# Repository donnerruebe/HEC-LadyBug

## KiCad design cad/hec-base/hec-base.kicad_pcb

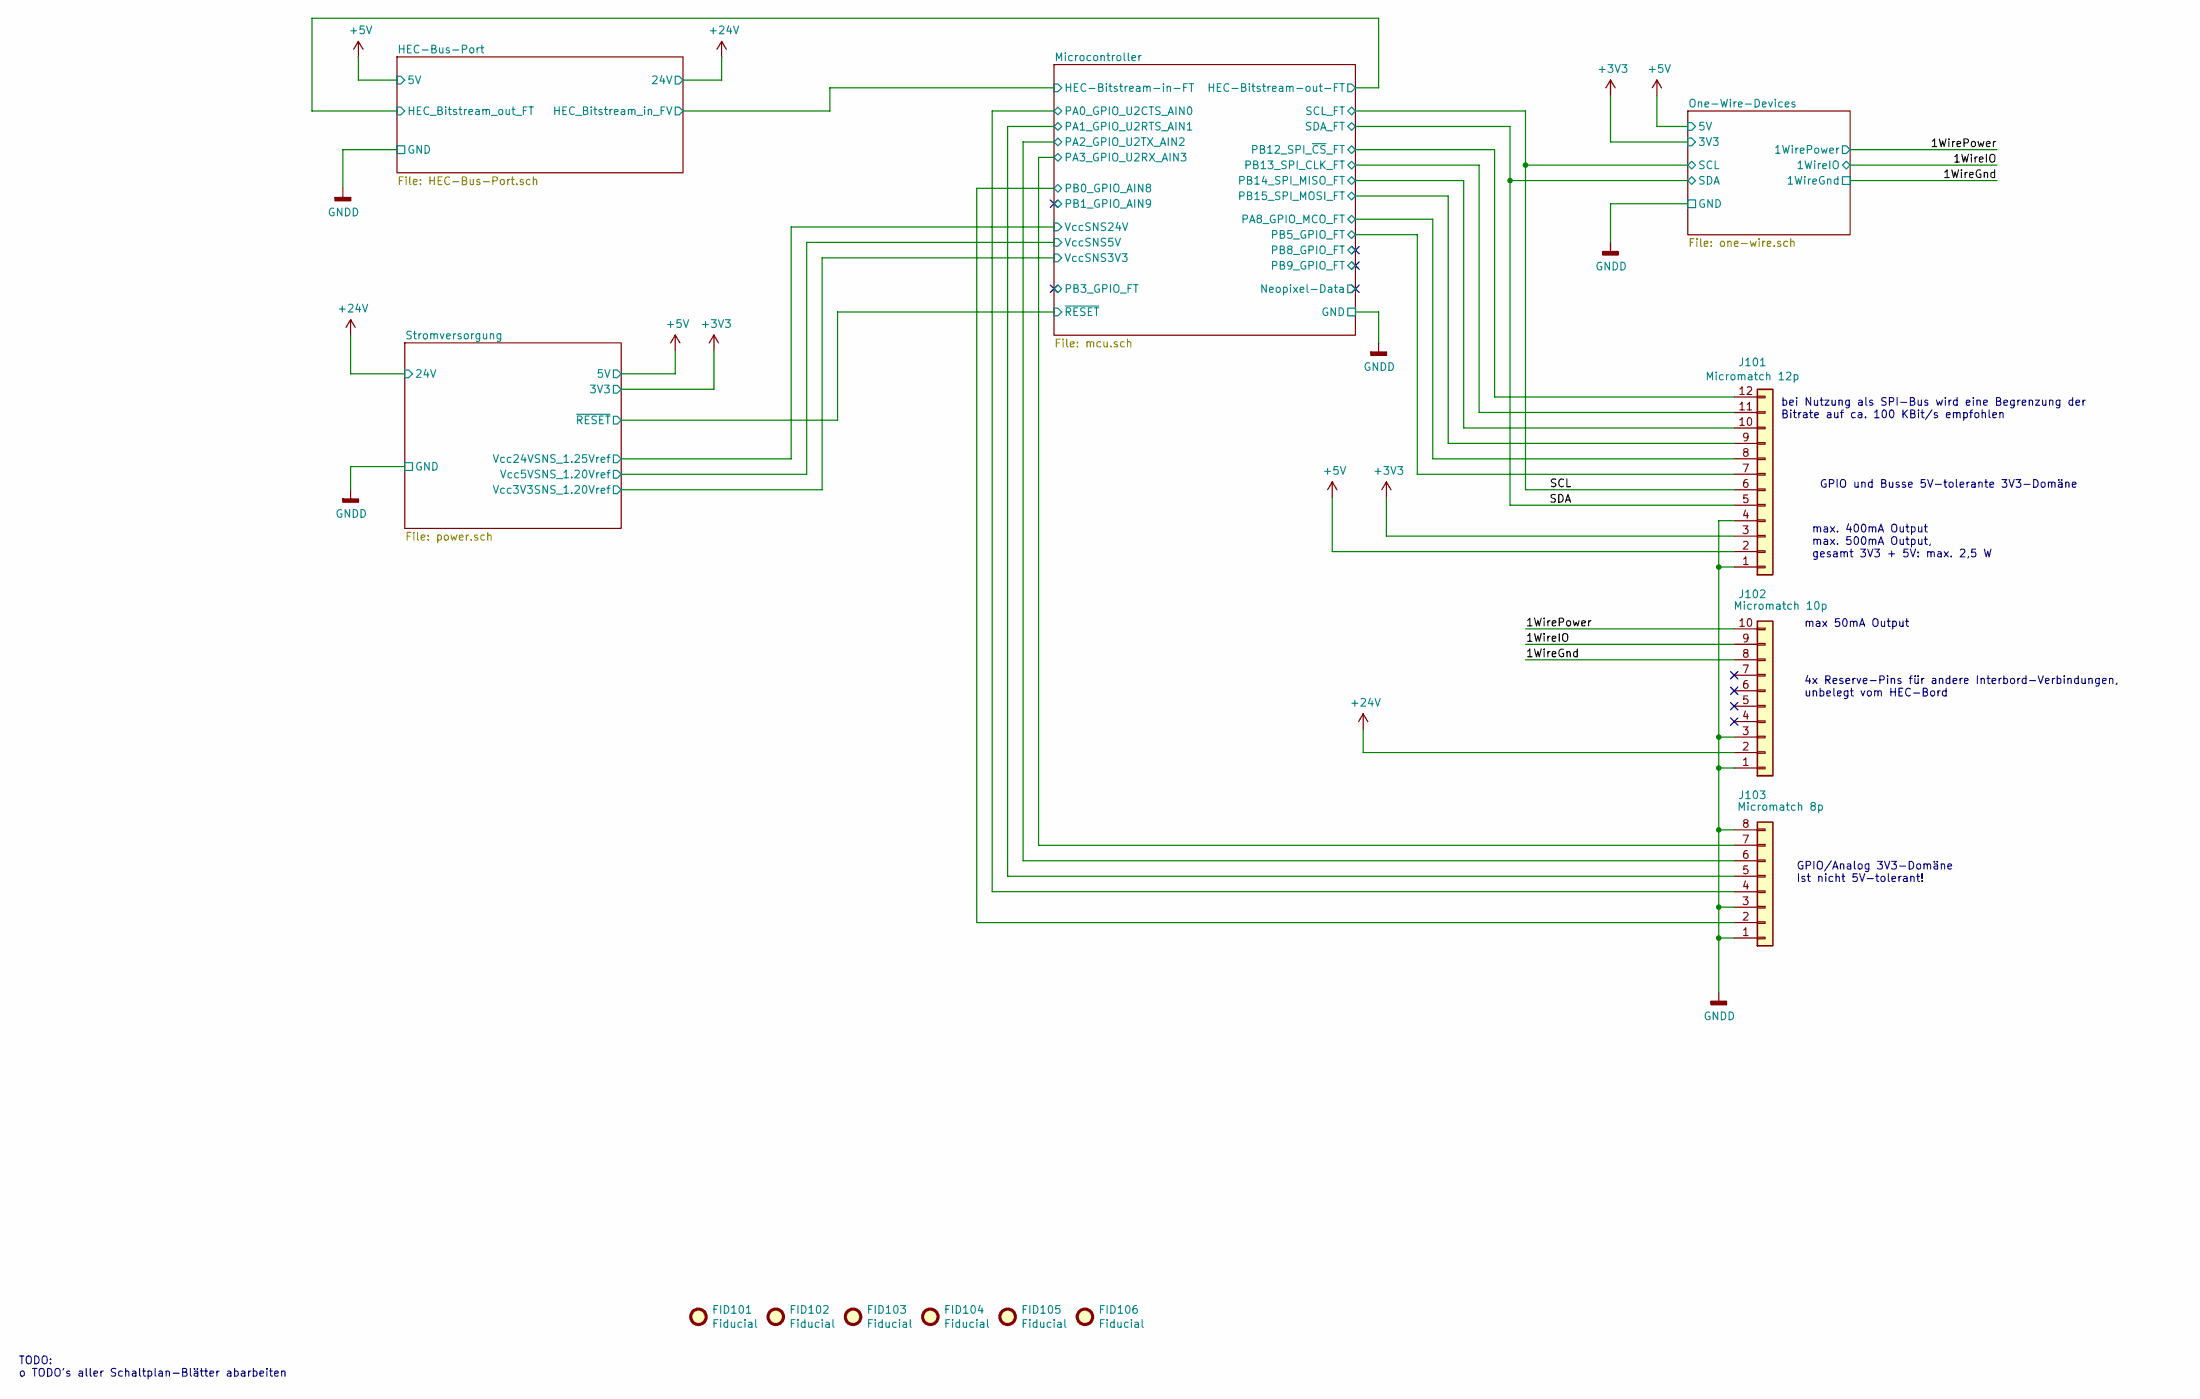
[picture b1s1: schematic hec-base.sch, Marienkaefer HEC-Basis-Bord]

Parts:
FID101, FID102, FID103, FID104, FID105, FID106: Fiducial; Fiducial_0.5mm_Mask1mm
J101: Micromatch 12p; ConnectorMicromatch-12-horizontal-THT
J102: Micromatch 10p; ConnectorMicromatch-10-horizontal-THT
J103: Micromatch 8p; ConnectorMicromatch-8-SMD-polarized

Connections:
+3V3: J101.3; also elsewhere on the board
+5V: J101.2; also elsewhere on the board
+24V: J102.2; also elsewhere on the board
/1WireIO: J102.9; also elsewhere on the board
/1WirePower: J102.10; also elsewhere on the board
/Microcontroller/PA0_GPIO_U2CTS_AIN0: J103.4; also elsewhere on the board
/Microcontroller/PA1_GPIO_U2RTS_AIN1: J103.5; also elsewhere on the board
/Microcontroller/PA2_GPIO_U2TX_AIN2: J103.6; also elsewhere on the board
/Microcontroller/PA3_GPIO_U2RX_AIN3: J103.7; also elsewhere on the board
/Microcontroller/PA8_GPIO_MCO_FT: J101.8; also elsewhere on the board
/Microcontroller/PB0_GPIO_AIN8: J103.2; also elsewhere on the board
/Microcontroller/PB5_GPIO_FT: J101.7; also elsewhere on the board
/Microcontroller/PB12_SPI_~CS~_FT: J101.12; also elsewhere on the board
/Microcontroller/PB13_SPI_CLK_FT: J101.11; also elsewhere on the board
/Microcontroller/PB14_SPI_MISO_FT: J101.10; also elsewhere on the board
/Microcontroller/PB15_SPI_MOSI_FT: J101.9; also elsewhere on the board
/SCL: J101.6; also elsewhere on the board
/SDA: J101.5; also elsewhere on the board
GNDD: J101.1, J101.4, J102.1, J102.3, J102.8, J103.1, J103.3, J103.8; also elsewhere on the board

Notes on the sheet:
bei Nutzung als SPI-Bus wird eine Begrenzung der Bitrate auf ca. 100 KBit/s empfohlen
GPIO/Analog 3V3-Domäne Ist nicht 5V-tolerant!
GPIO und Busse 5V-tolerante 3V3-Domäne
4x Reserve-Pins für andere Interbord-Verbindungen, unbelegt vom HEC-Bord
max. 400mA Output max. 500mA Output, gesamt 3V3 + 5V: max. 2,5 W
max 50mA Output
TODO: o TODO's aller Schaltplan-Blätter abarbeiten

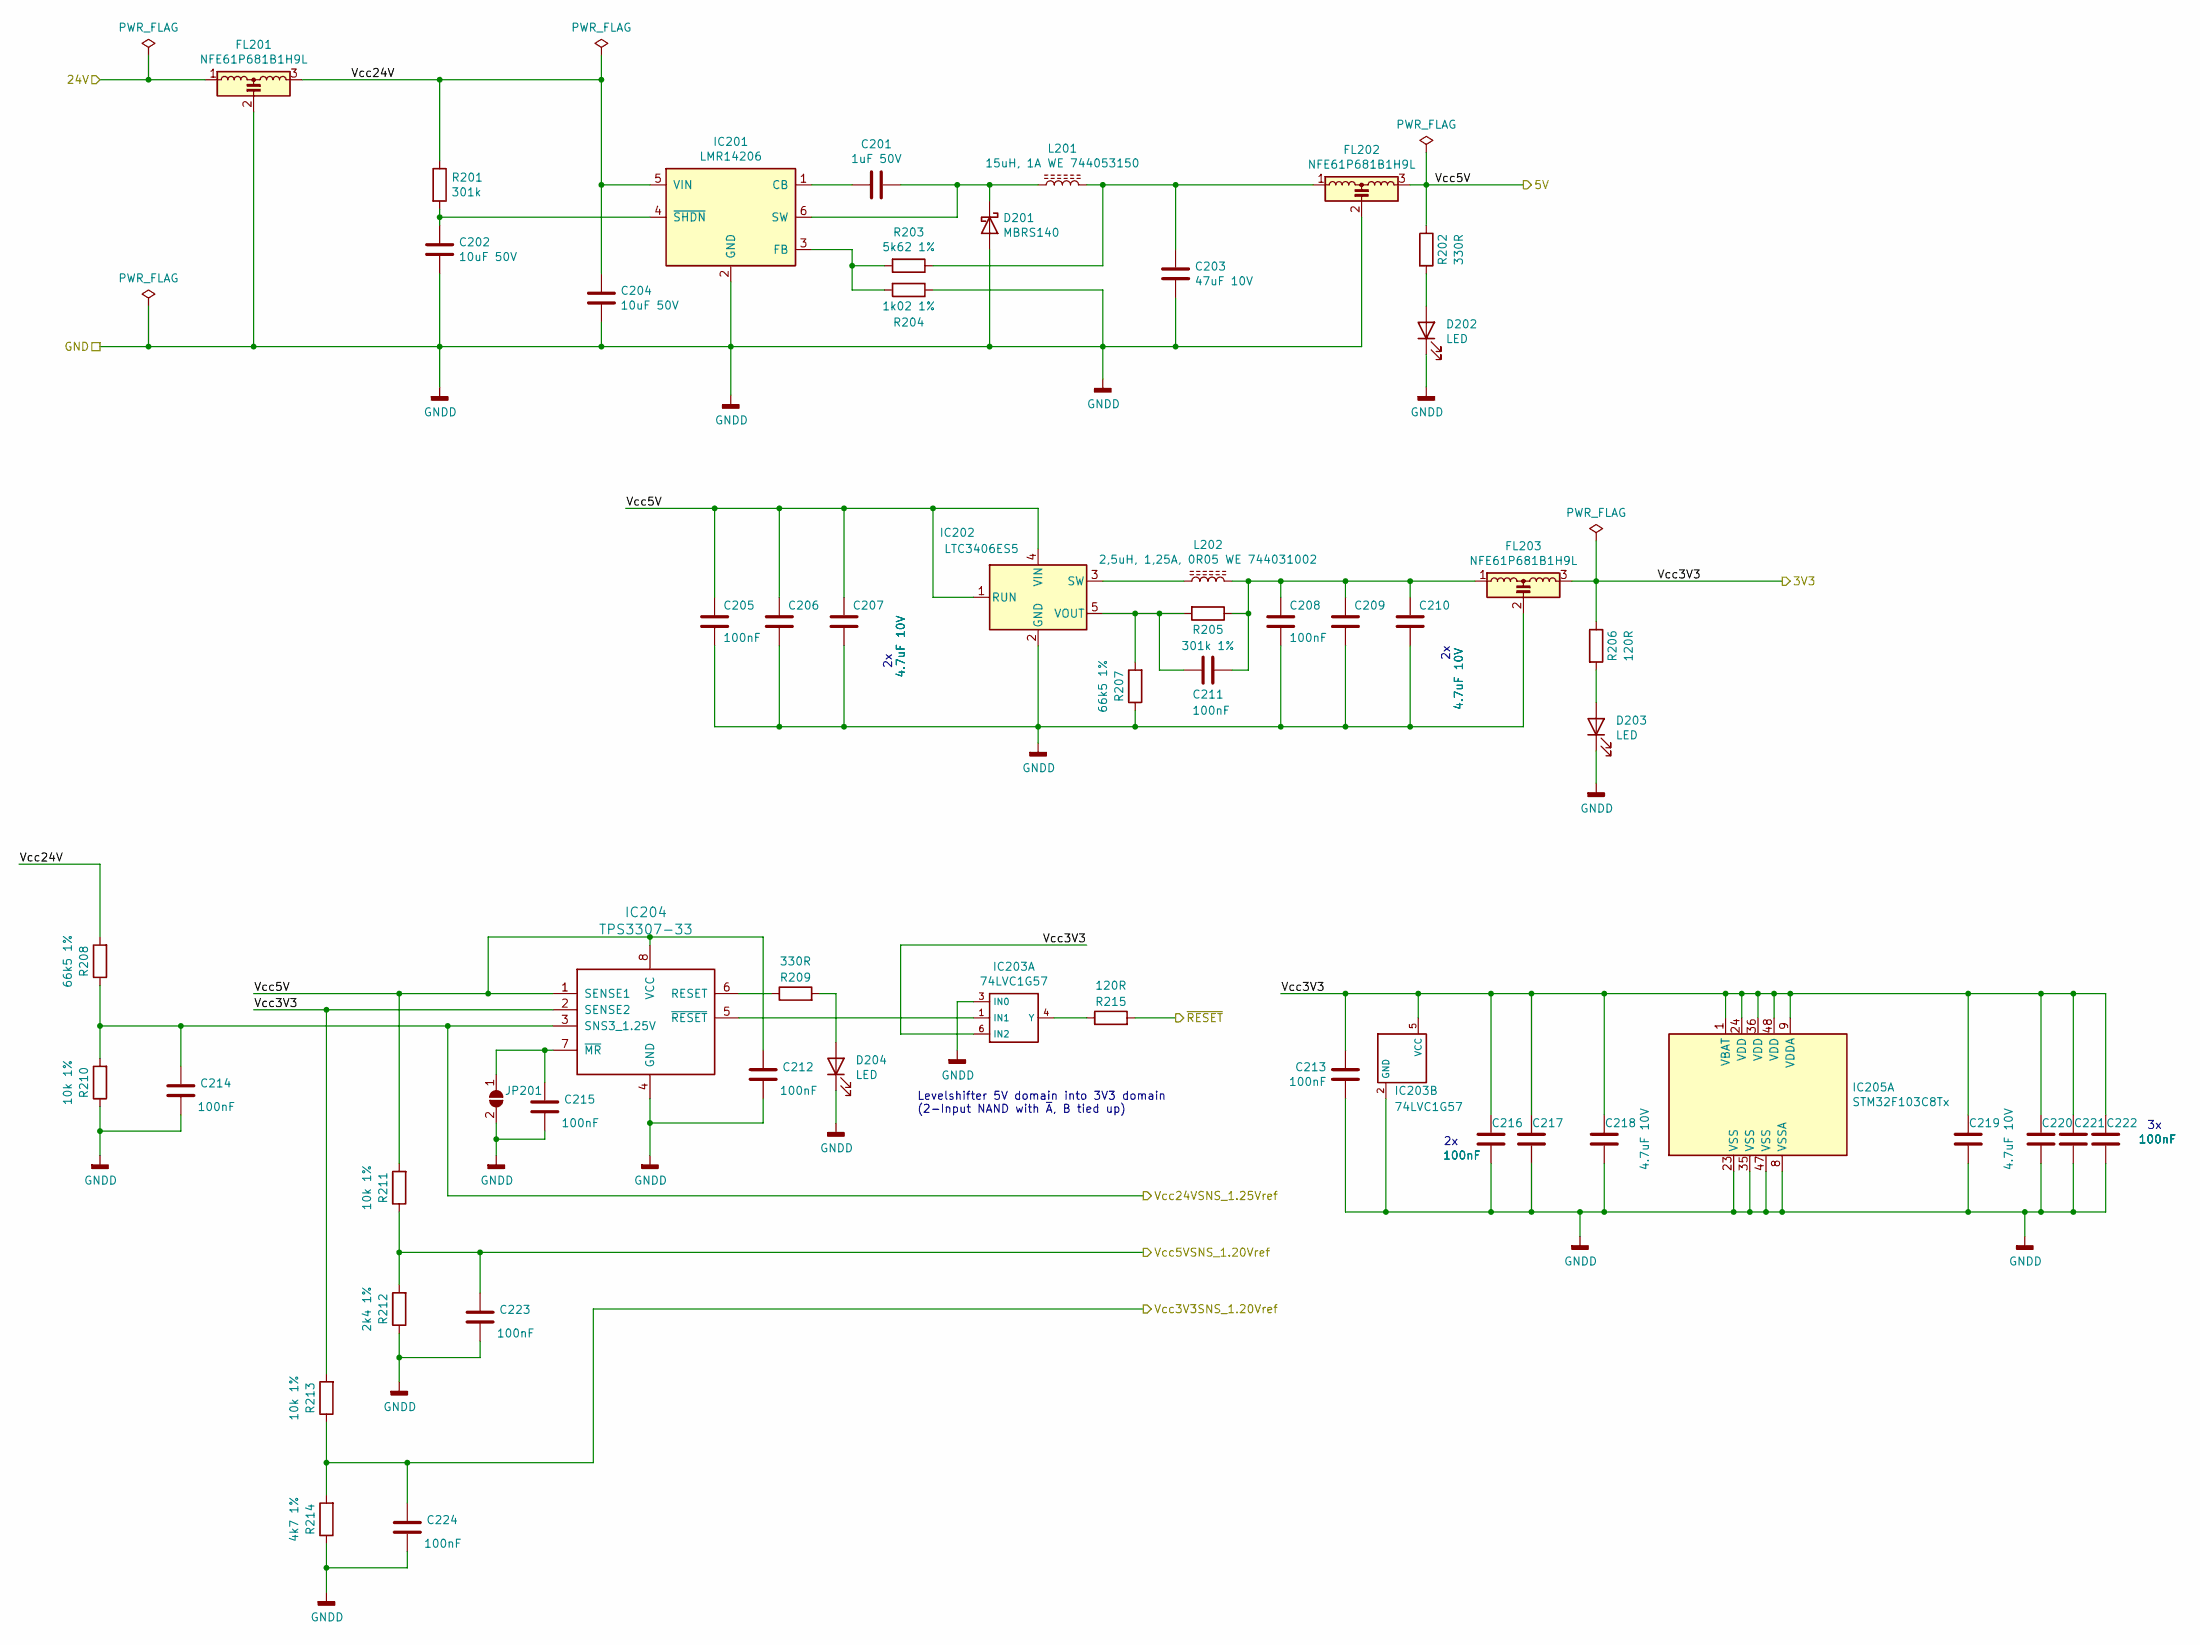
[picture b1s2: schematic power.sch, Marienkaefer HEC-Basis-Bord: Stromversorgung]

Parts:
C201: 1uF 50V; C_0805_2012Metric
C202, C204: 10uF 50V; C_1206_3216Metric
C203: 47uF 10V; C_1210_3225Metric
C205, C208, C211, C212, C213, C214, C215, C216, C217, C220, C221, C222, C223, C224: 100nF; C_0603_1608Metric
C206, C207, C209, C210, C218, C219: 4.7uF 10V; C_0805_2012Metric
D201: MBRS140; D_SMB
D202, D203, D204: LED; LED_0603_1608Metric
FL201, FL202, FL203: NFE61P681B1H9L; Murata_NFE61P
IC201: LMR14206; SOT-23-6
IC202: LTC3406ES5; TSOT-23-5
IC203: 74LVC1G57; SOT-363_SC-70-6
IC204: TPS3307-33; SO-8_3.9x4.9mm_P1.27mm
IC205: STM32F103C8Tx; LQFP-48_7x7mm_P0.5mm
JP201: SolderJumper_2_Open; SolderJumper-2_P1.3mm_Open_RoundedPad1.0x1.5mm
L201: 15uH, 1A WE 744053150; L_Wuerth_WE-TPC-3816
L202: 2,5uH, 1,25A, 0R05 WE 744031002; L_Wuerth_WE-TPC-3816
R201: 301k; R_0603_1608Metric
R202, R209: 330R; R_0603_1608Metric
R203: 5k62 1%; R_0603_1608Metric
R204: 1k02 1%; R_0603_1608Metric
R205: 301k 1%; R_0603_1608Metric
R206, R215: 120R; R_0603_1608Metric
R207, R208: 66k5 1%; R_0603_1608Metric
R210, R211, R213: 10k 1%; R_0603_1608Metric
R212: 2k4 1%; R_0603_1608Metric
R214: 4k7 1%; R_0603_1608Metric

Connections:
+3V3: C213.2, C216.2, C217.2, C218.2, C219.2, C220.2, C221.2, C222.2, FL203.3, IC203.5 (VCC), IC203.6 (IN2), IC204.2 (SENSE2), IC205.1 (VBAT), IC205.9 (VDDA), IC205.24 (VDD), IC205.36 (VDD), IC205.48 (VDD), R206.1, R213.2; also elsewhere on the board
+5V: C205.2, C206.2, C207.2, C212.2, FL202.3, IC202.1 (RUN), IC202.4 (VIN), IC204.1 (SENSE1), IC204.8 (VCC), R202.1, R211.2; also elsewhere on the board
+24V: FL201.1; also elsewhere on the board
/Microcontroller/~RESET~: R215.2; also elsewhere on the board
/Stromversorgung/Vcc3V3SNS_1.20Vref: C224.2, R213.1, R214.2; also elsewhere on the board
/Stromversorgung/Vcc5VSNS_1.20Vref: C223.2, R211.1, R212.2; also elsewhere on the board
/Stromversorgung/Vcc24V: C204.1, FL201.3, IC201.5 (VIN), R201.1, R208.2
/Stromversorgung/Vcc24VSNS_1.25Vref: C214.2, IC204.3 (SNS3_1.25V), R208.1, R210.2; also elsewhere on the board
GNDD: C202.1, C203.2, C204.2, C205.1, C206.1, C207.1, C208.1, C209.1, C210.1, C212.1, C213.1, C214.1, C215.1, C216.1, C217.1, C218.1, C219.1, C220.1, C221.1, C222.1, C223.1, C224.1, D201.2 (A), D202.1 (K), D203.1 (K), D204.1 (K), FL201.2, FL202.2, FL203.2, IC201.2 (GND), IC202.2 (GND), IC203.2 (GND), IC203.3 (IN0), IC204.4 (GND), IC205.8 (VSSA), IC205.23 (VSS), IC205.35 (VSS), IC205.47 (VSS), JP201.2 (B), R204.1, R207.1, R210.1, R212.1, R214.1; also elsewhere on the board
unnamed: C201.1, D201.1 (K), IC201.6 (SW), L201.1
unnamed: C201.2, IC201.1 (CB)
unnamed: C202.2, IC201.4 (~SHDN), R201.2
unnamed: C203.1, FL202.1, L201.2, R203.1
unnamed: C208.2, C209.2, C210.2, C211.2, FL203.1, L202.2, R205.1
unnamed: C211.1, IC202.5 (VOUT), R205.2, R207.2
unnamed: C215.2, IC204.7 (~MR), JP201.1 (A)
unnamed: D202.2 (A), R202.2
unnamed: D203.2 (A), R206.2
unnamed: D204.2 (A), R209.2
unnamed: IC201.3 (FB), R203.2, R204.2
unnamed: IC202.3 (SW), L202.1
unnamed: IC203.1 (IN1), IC204.5 (~RESET)
unnamed: IC203.4 (Y), R215.1
unnamed: IC204.6 (RESET), R209.1

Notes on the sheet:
Levelshifter 5V domain into 3V3 domain (2-Input NAND with ~A~, B tied up)

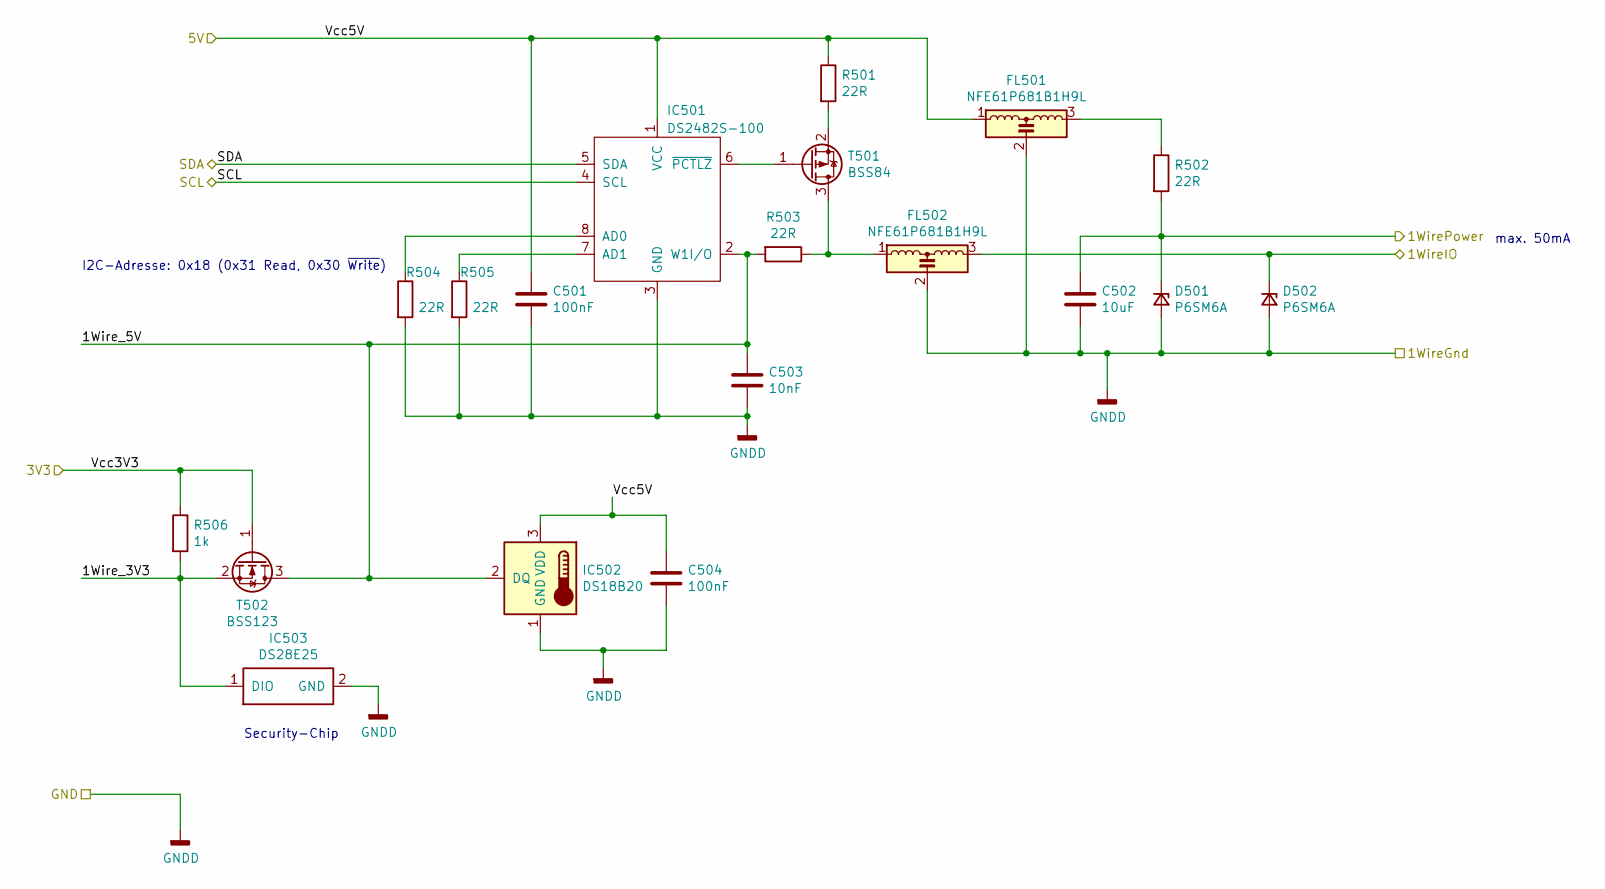
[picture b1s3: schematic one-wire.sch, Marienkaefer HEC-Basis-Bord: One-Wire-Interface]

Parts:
C501, C504: 100nF; C_0603_1608Metric
C502: 10uF; C_0805_2012Metric
C503: 10nF; C_0603_1608Metric
D501, D502: P6SM6A; D_SMB
FL501, FL502: NFE61P681B1H9L; Murata_NFE61P
IC501: DS2482S-100; SO-8_3.9x4.9mm_P1.27mm
IC502: DS18B20; TO-92_Inline
IC503: DS28E25; TO-92-2
R501, R502, R503, R504, R505: 22R; R_0603_1608Metric
R506: 1k; R_0603_1608Metric
T501: BSS84; SOT-23
T502: BSS123; SOT-23

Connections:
+3V3: R506.1, T502.1 (G); also elsewhere on the board
+5V: C501.1, C504.1, FL501.1, IC501.1 (VCC), IC502.3 (VDD), R501.1; also elsewhere on the board
/1WireIO: D502.1 (K), FL502.3; also elsewhere on the board
/1WirePower: C502.1, D501.1 (K), R502.2; also elsewhere on the board
/One-Wire-Devices/1Wire_3V3: IC503.1 (DIO), R506.2, T502.2 (S)
/One-Wire-Devices/1Wire_5V: C503.1, IC501.2 (W1I/O), IC502.2 (DQ), R503.2, T502.3 (D)
/SCL: IC501.4 (SCL); also elsewhere on the board
/SDA: IC501.5 (SDA); also elsewhere on the board
GNDD: C501.2, C502.2, C503.2, C504.2, D501.2 (A), D502.2 (A), FL501.2, FL502.2, IC501.3 (GND), IC502.1 (GND), IC503.2 (GND), R504.2, R505.2; also elsewhere on the board
unnamed: FL501.3, R502.1
unnamed: FL502.1, R503.1, T501.3 (D)
unnamed: IC501.6 (~PCTLZ~), T501.1 (G)
unnamed: IC501.7 (AD1), R505.1
unnamed: IC501.8 (AD0), R504.1
unnamed: R501.2, T501.2 (S)

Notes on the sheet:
max. 50mA
I2C-Adresse: 0x18 (0x31 Read, 0x30 ~Write~)
Security-Chip

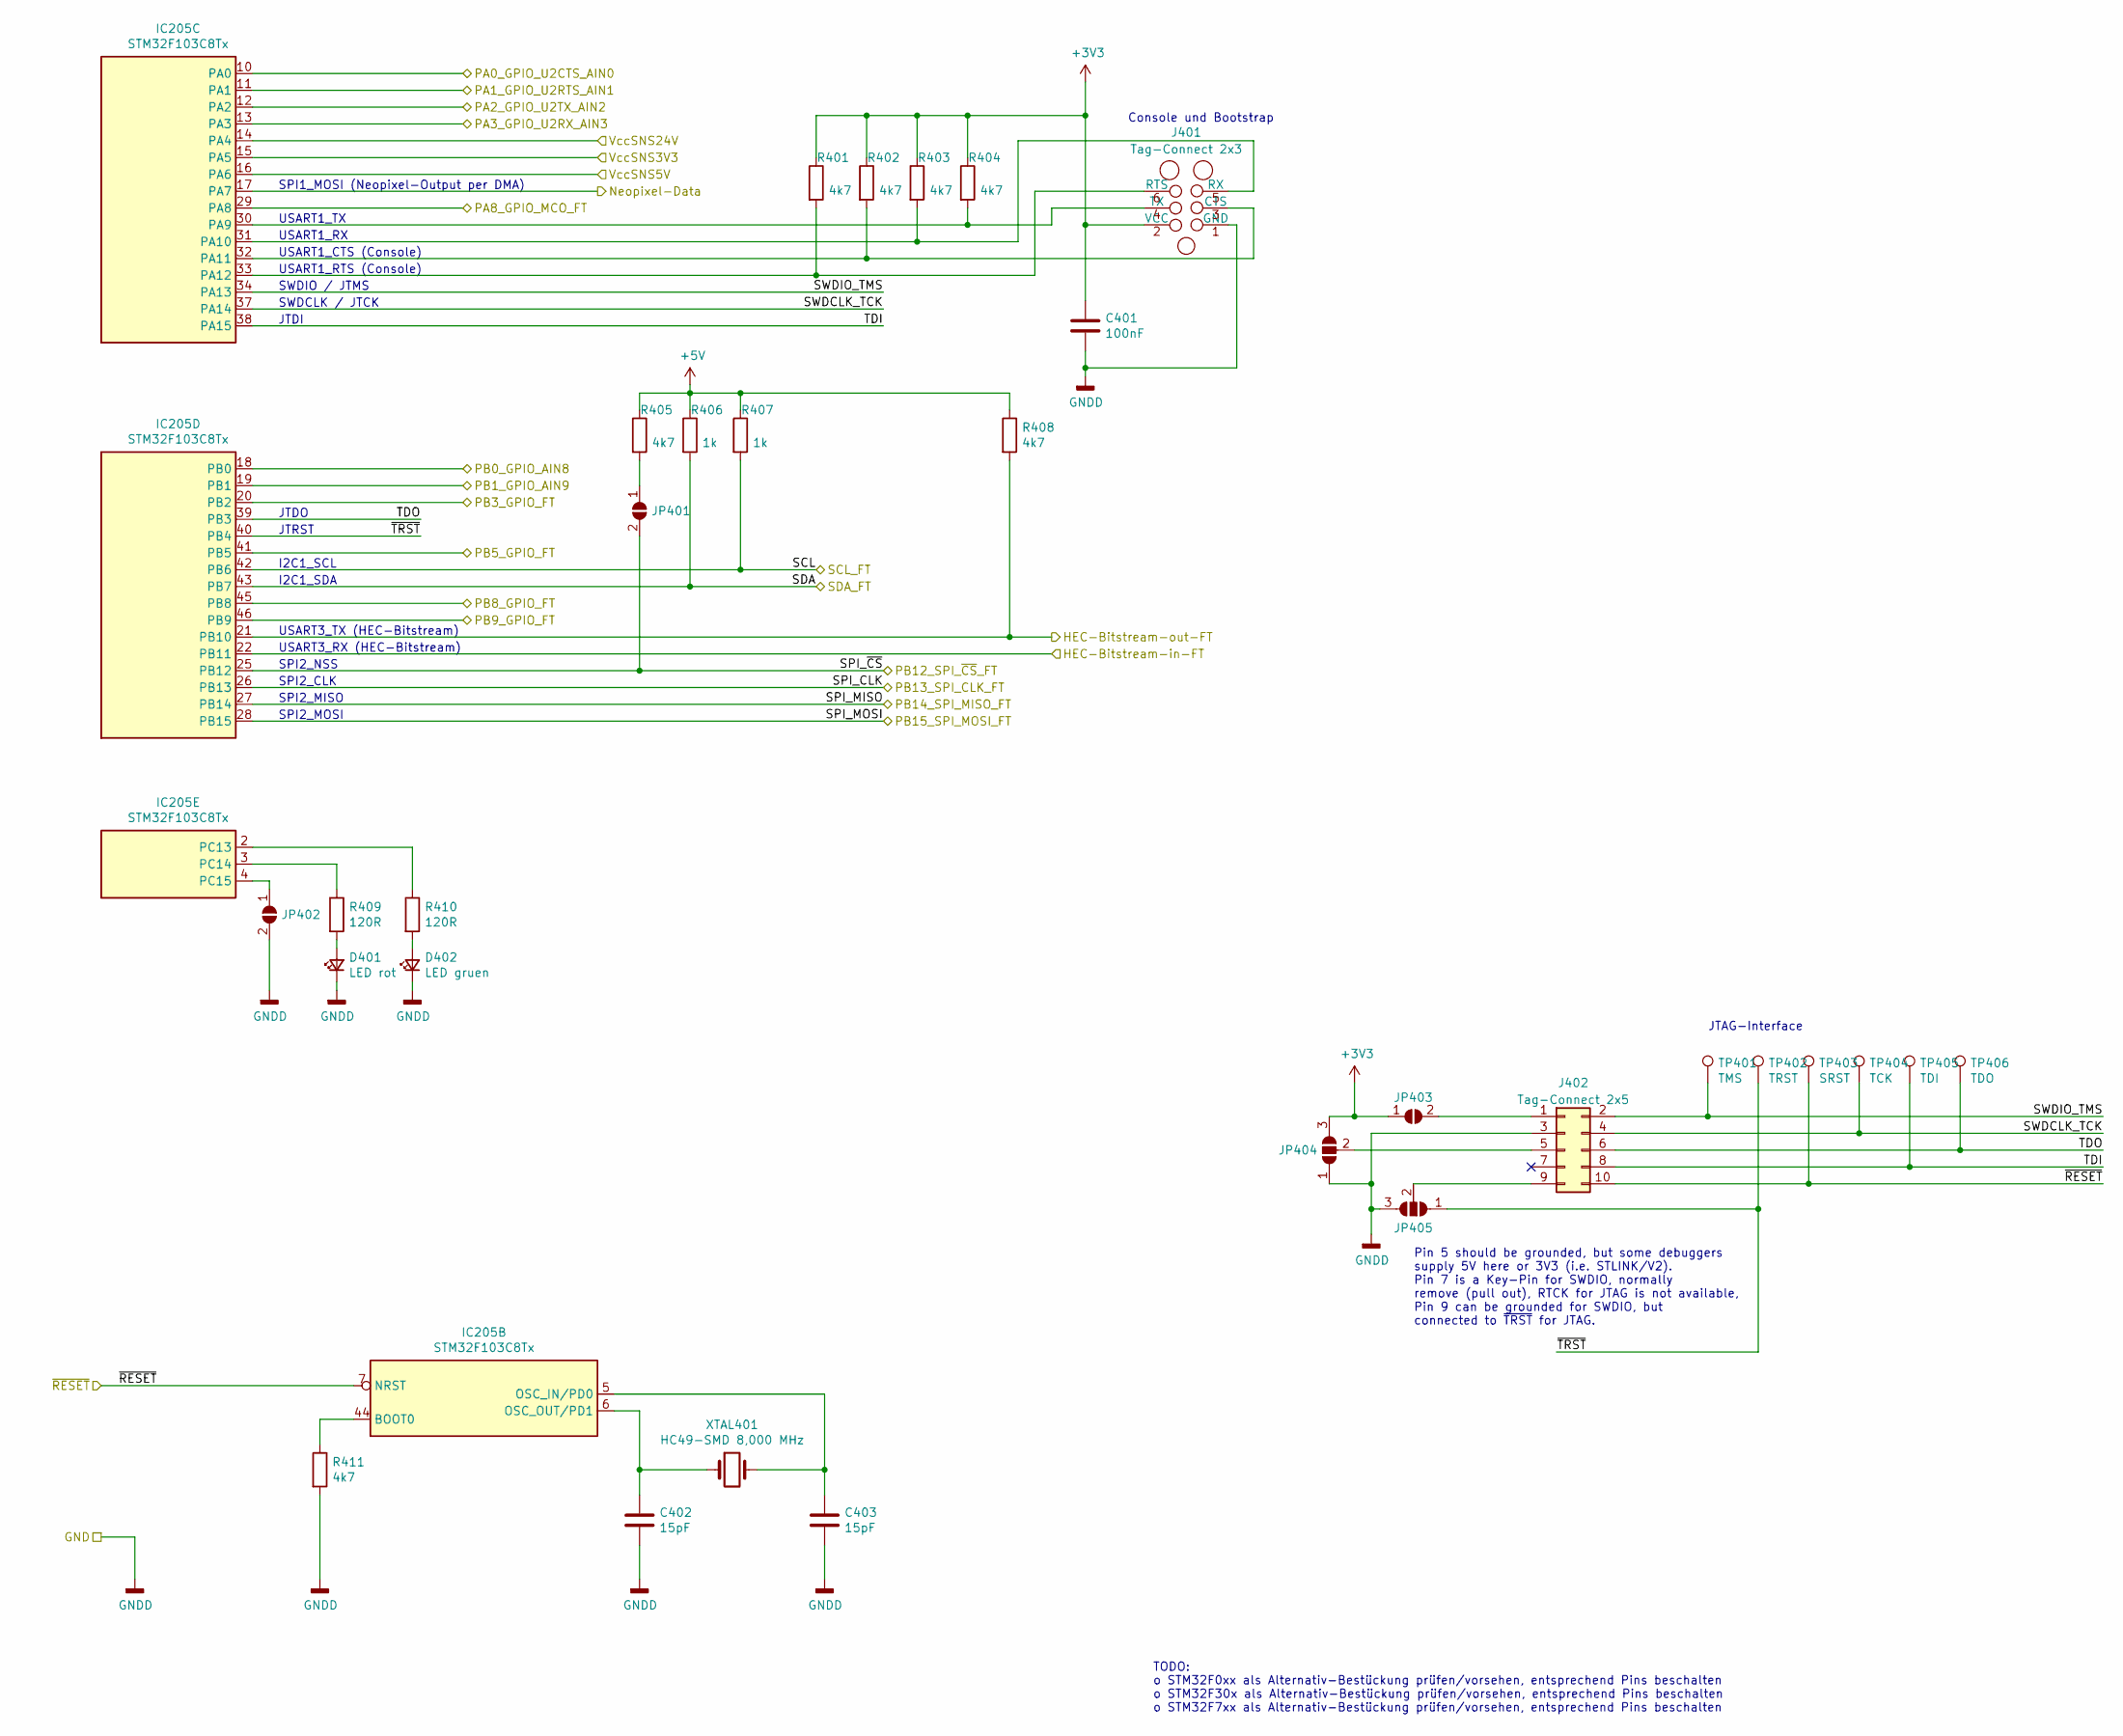
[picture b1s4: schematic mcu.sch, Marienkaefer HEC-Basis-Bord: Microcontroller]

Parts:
C401: 100nF; C_0603_1608Metric
C402, C403: 15pF; C_0603_1608Metric
D401: LED rot; LED_0603_1608Metric
D402: LED gruen; LED_0603_1608Metric
IC205: STM32F103C8Tx; LQFP-48_7x7mm_P0.5mm
J401: Tag-Connect 2x3; Tag-Connect_TC2030-IDC-NL_2x03_P1.27mm_Vertical
J402: Tag-Connect 2x5; Tag-Connect_TC2050-IDC-NL_2x05_P1.27mm_Vertical
JP401, JP403: SolderJumper_2_Open; SolderJumper-2_P1.3mm_Open_TrianglePad1.0x1.5mm
JP402: SolderJumper_2_Open; SolderJumper-2_P1.3mm_Open_RoundedPad1.0x1.5mm
JP404, JP405: SolderJumper_3_Open; SolderJumper-3_P1.3mm_Open_RoundedPad1.0x1.5mm_NumberLabels
R401, R402, R403, R404, R405, R408, R411: 4k7; R_0603_1608Metric
R406, R407: 1k; R_0603_1608Metric
R409, R410: 120R; R_0603_1608Metric
TP401: TMS; TestPoint_Pad_D1.0mm
TP402: TRST; TestPoint_Pad_D1.0mm
TP403: SRST; TestPoint_Pad_D1.0mm
TP404: TCK; TestPoint_Pad_D1.0mm
TP405: TDI; TestPoint_Pad_D1.0mm
TP406: TDO; TestPoint_Pad_D1.0mm
XTAL401: HC49-SMD 8,000 MHz; Crystal_SMD_HC49-SD

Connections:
+3V3: C401.1, J401.2 (VCC), JP403.1 (A), JP404.3 (B), R401.1, R402.1, R403.1, R404.1; also elsewhere on the board
+5V: R405.1, R406.1, R407.1, R408.1; also elsewhere on the board
/Microcontroller/HEC-Bitstream-in-FT: IC205.22 (PB11); also elsewhere on the board
/Microcontroller/HEC-Bitstream-out-FT: IC205.21 (PB10), R408.2; also elsewhere on the board
/Microcontroller/PA0_GPIO_U2CTS_AIN0: IC205.10 (PA0); also elsewhere on the board
/Microcontroller/PA1_GPIO_U2RTS_AIN1: IC205.11 (PA1); also elsewhere on the board
/Microcontroller/PA2_GPIO_U2TX_AIN2: IC205.12 (PA2); also elsewhere on the board
/Microcontroller/PA3_GPIO_U2RX_AIN3: IC205.13 (PA3); also elsewhere on the board
/Microcontroller/PA8_GPIO_MCO_FT: IC205.29 (PA8); also elsewhere on the board
/Microcontroller/PB0_GPIO_AIN8: IC205.18 (PB0); also elsewhere on the board
/Microcontroller/PB5_GPIO_FT: IC205.41 (PB5); also elsewhere on the board
/Microcontroller/PB12_SPI_~CS~_FT: IC205.25 (PB12), JP401.2 (B); also elsewhere on the board
/Microcontroller/PB13_SPI_CLK_FT: IC205.26 (PB13); also elsewhere on the board
/Microcontroller/PB14_SPI_MISO_FT: IC205.27 (PB14); also elsewhere on the board
/Microcontroller/PB15_SPI_MOSI_FT: IC205.28 (PB15); also elsewhere on the board
/Microcontroller/SWDCLK_TCK: IC205.37 (PA14), J402.4, TP404.1
/Microcontroller/SWDIO_TMS: IC205.34 (PA13), J402.2, TP401.1
/Microcontroller/TDI: IC205.38 (PA15), J402.8, TP405.1
/Microcontroller/TDO: IC205.39 (PB3), J402.6, TP406.1
/Microcontroller/~RESET~: IC205.7 (NRST), J402.10, TP403.1; also elsewhere on the board
/Microcontroller/~TRST~: IC205.40 (PB4), JP405.1 (A), TP402.1
/SCL: IC205.42 (PB6), R407.2; also elsewhere on the board
/SDA: IC205.43 (PB7), R406.2; also elsewhere on the board
/Stromversorgung/Vcc3V3SNS_1.20Vref: IC205.15 (PA5); also elsewhere on the board
/Stromversorgung/Vcc5VSNS_1.20Vref: IC205.16 (PA6); also elsewhere on the board
/Stromversorgung/Vcc24VSNS_1.25Vref: IC205.14 (PA4); also elsewhere on the board
GNDD: C401.2, C402.2, C403.2, D401.1 (K), D402.1 (K), J401.1 (GND), J402.3, JP402.2 (B), JP404.1 (A), JP405.3 (B), R411.2; also elsewhere on the board
unnamed: C402.1, IC205.6 (OSC_OUT/PD1), XTAL401.1
unnamed: C403.1, IC205.5 (OSC_IN/PD0), XTAL401.2
unnamed: D401.2 (A), R409.2
unnamed: D402.2 (A), R410.2
unnamed: IC205.2 (PC13), R410.1
unnamed: IC205.3 (PC14), R409.1
unnamed: IC205.4 (PC15), JP402.1 (A)
unnamed: IC205.30 (PA9), J401.4 (TX), R404.2
unnamed: IC205.31 (PA10), J401.5 (RX), R403.2
unnamed: IC205.32 (PA11), J401.3 (CTS), R402.2
unnamed: IC205.33 (PA12), J401.6 (RTS), R401.2
unnamed: IC205.44 (BOOT0), R411.1
unnamed: J402.1, JP403.2 (B)
unnamed: J402.5, JP404.2 (C)
unnamed: J402.9, JP405.2 (C)
unnamed: JP401.1 (A), R405.2

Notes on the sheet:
USART1_TX
USART1_RX
USART1_CTS (Console)
USART1_RTS (Console)
SWDIO / JTMS
SWDCLK / JTCK
JTDI
SPI2_NSS
SPI2_CLK
SPI2_MISO
SPI2_MOSI
I2C1_SCL
I2C1_SDA
USART3_TX (HEC-Bitstream)
USART3_RX (HEC-Bitstream)
SPI1_MOSI (Neopixel-Output per DMA)
JTAG-Interface
Pin 5 should be grounded, but some debuggers supply 5V here or 3V3 (i.e. STLINK/V2). Pin 7 is a Key-Pin for SWDIO, normally remove (pull out), RTCK for JTAG is not available, Pin 9 can be grounded for SWDIO, but connected to ~TRST~ for JTAG.
JTRST
JTDO
Console und Bootstrap
TODO: o STM32F0xx als Alternativ-Bestückung prüfen/vorsehen, entsprechend Pins beschalten o STM32F30x als Alternativ-Bestückung prüfen/vorsehen, entsprechend Pins beschalten o STM32F7xx als Alternativ-Bestückung prüfen/vorsehen, entsprechend Pins beschalten

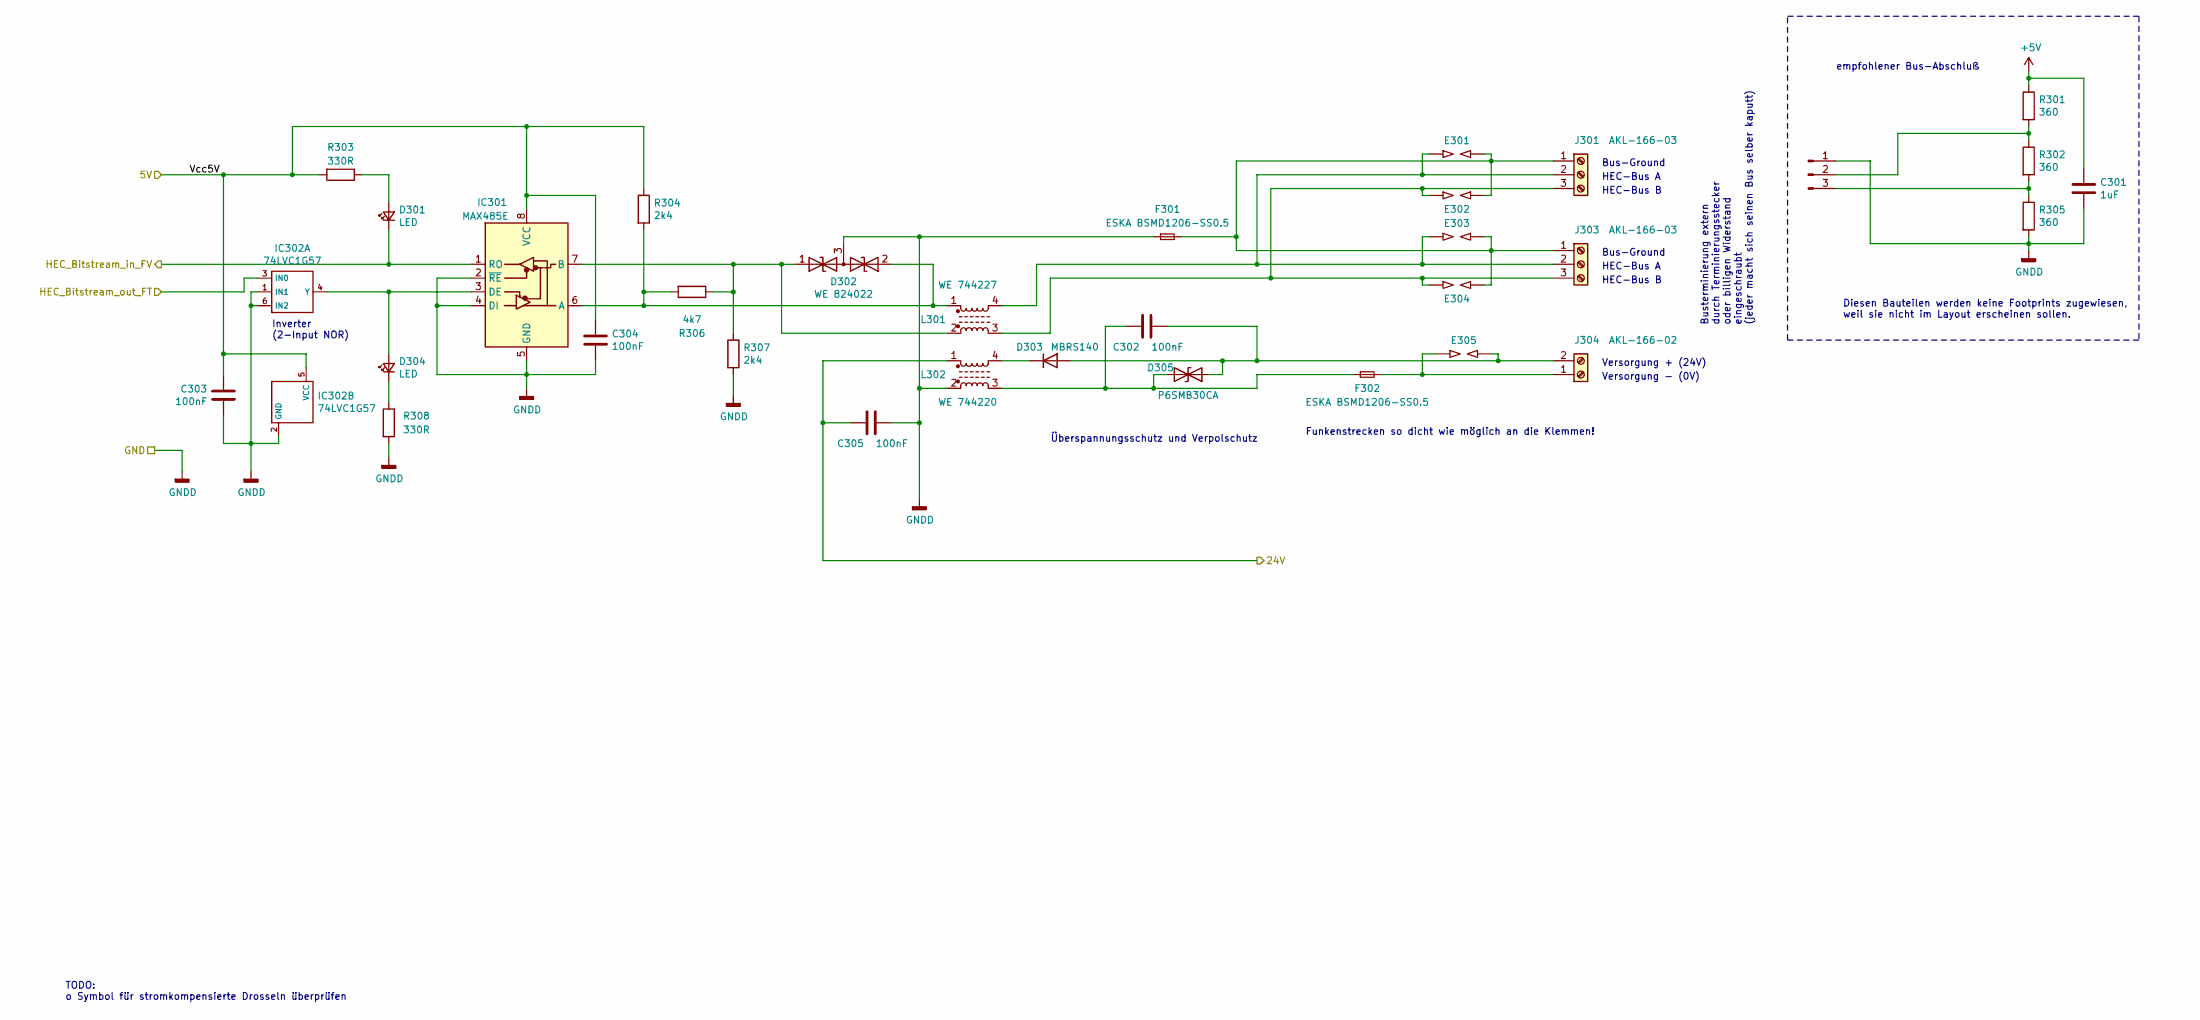
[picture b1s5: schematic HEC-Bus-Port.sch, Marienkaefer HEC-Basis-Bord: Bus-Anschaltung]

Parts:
C301: 1uF
C302, C303, C304, C305: 100nF; C_0603_1608Metric
D301, D304: LED; LED_0603_1608Metric
D302: WE 824022; SOT-23
D303: MBRS140; D_SMB
D305: P6SMB30CA; D_SMB
E301, E302, E303, E304, E305: SPARK_GAP; SparkGap_3pin_0.67x0.5mm
F301, F302: ESKA BSMD1206-SS0.5; R_1206_3216Metric
IC301: MAX485E; SO-8_3.9x4.9mm_P1.27mm
IC302: 74LVC1G57; SOT-363_SC-70-6
J301, J303: AKL-166-03; TerminalBlock_MetzConnect_Type059_RT06303HBWC_1x03_P3.50mm_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
J302: Conn_01x03_Male
J304: AKL-166-02; TerminalBlock_MetzConnect_Type059_RT06302HBWC_1x02_P3.50mm_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
L301: WE 744227; L_CommonMode_Wuerth_WE-SL2
L302: WE 744220; L_CommonMode_Wuerth_WE-SL2
R301, R302, R305: 360
R303, R308: 330R; R_0603_1608Metric
R304, R307: 2k4; R_0603_1608Metric
R306: 4k7; R_0603_1608Metric

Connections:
+5V: C303.1, C304.1, IC301.8 (VCC), IC302.5 (VCC), R303.2, R304.1; also elsewhere on the board
+24V: C305.2, L302.1; also elsewhere on the board
/Microcontroller/HEC-Bitstream-in-FT: D301.1 (K), IC301.1 (RO); also elsewhere on the board
/Microcontroller/HEC-Bitstream-out-FT: IC302.3 (IN0); also elsewhere on the board
GNDD: C301.2, C303.2, C304.2, C305.1, D302.3 (common), F301.1, IC301.2 (~RE), IC301.4 (DI), IC301.5 (GND), IC302.1 (IN1), IC302.2 (GND), IC302.6 (IN2), J302.1, L302.2, R305.2, R307.2, R308.2; also elsewhere on the board
unnamed: C301.1, R301.1
unnamed: C302.1, D303.2 (A), D305.1 (A1), E305.2, J304.2
unnamed: C302.2, D305.2 (A2), F302.1, L302.3
unnamed: D301.2 (A), R303.1
unnamed: D302.1 (A1), IC301.7 (B), L301.2, R306.1, R307.1
unnamed: D302.2 (A2), IC301.6 (A), L301.1, R304.2, R306.2
unnamed: D303.1 (K), L302.4
unnamed: D304.1 (K), R308.1
unnamed: D304.2 (A), IC301.3 (DE), IC302.4 (Y)
unnamed: E301.1, E303.1, J301.2, J303.2, L301.4
unnamed: E301.2, E302.2, E303.2, E304.2, F301.2, J301.1, J303.1
unnamed: E302.1, E304.1, J301.3, J303.3, L301.3
unnamed: E305.1, F302.2, J304.1
unnamed: J302.2, R301.2, R302.1
unnamed: J302.3, R302.2, R305.1

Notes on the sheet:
Bus-Ground
Versorgung + (24V)
Versorgung - (0V)
HEC-Bus B
HEC-Bus A
Busterminierung extern durch Terminierungsstecker oder billigen Widerstand eingeschraubt (jeder macht sich seinen Bus selber kaputt)
Funkenstrecken so dicht wie möglich an die Klemmen!
TODO: o Symbol für stromkompensierte Drosseln überprüfen
Überspannungsschutz und Verpolschutz
empfohlener Bus-Abschluß
Diesen Bauteilen werden keine Footprints zugewiesen, weil sie nicht im Layout erscheinen sollen.
Inverter (2-Input NOR)
